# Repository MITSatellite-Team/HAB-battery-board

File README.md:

# HAB-battery-board

Battery board for the MIT Satellite team. Takes in a 2S LiPo and outputs 3.3V + BAT after protecting from overvoltage and undervoltage.

> Made by Nathan Alspaugh
(ndal@mit.edu)

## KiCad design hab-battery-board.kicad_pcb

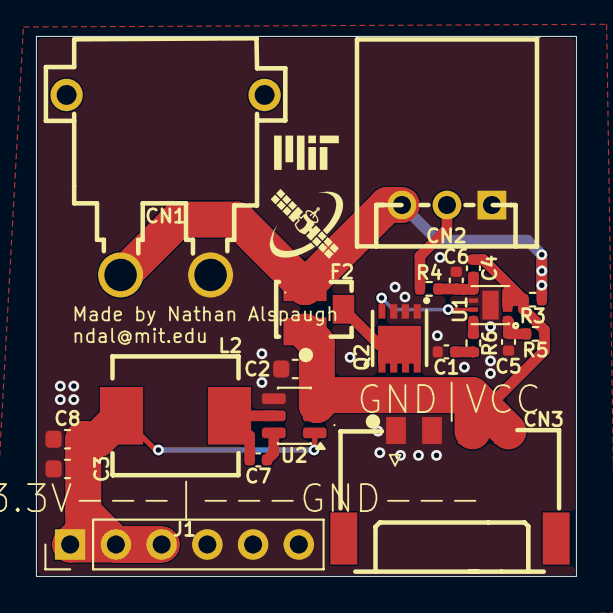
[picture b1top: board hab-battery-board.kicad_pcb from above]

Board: 2 copper layers, 30.0 x 30.0 mm, 21 parts (0 on the bottom side), 13 nets.

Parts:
C1: 470nF; C_0402_1005Metric
C2: 10uF; C_0603_1608Metric
C3, C8: 22uF; C_0603_1608Metric
C4, C5, C6, C7: 100nF; C_0402_1005Metric
CN1: XT30PW-M; CONN-TH_XT30PW-M
CN2: S3B-XH-A; CONN-TH_S3B-XH-A-LF-SN
CN3: 2053380004; CONN-SMD_3P_2053380004
F2: WSFB1514; FUSE-SMD_L4.0-W3.0_SFJ-1412
J1: Conn_01x06_Pin; PinHeader_1x06_P2.54mm_Vertical
L2: FXL0630-4R7-M; IND-SMD_L7.0-W6.6
Q2: AON7506; DFN-8_L3.0-W3.0-P0.65-BL
R3, R4: 1K; R_0402_1005Metric
R5: 100R; R_0402_1005Metric
R6: 5R; R_0402_1005Metric
U1: BQ296227DSGR; WSON-8_L2.0-W2.0-P0.50-TL-EP
U2: AP63203WU; TSOT-23-6

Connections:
+3.3V: C3.1, C8.1, J1.1, J1.2, J1.3, L2.2, U2.1 (FB)
/BAT+: CN1.2 (+), CN2.3, F2.2, R3.1
/BAT_MID: CN2.2, R4.1
GND: C1.2, C2.2, C3.2, C5.2, C6.1, C8.2, CN1.1 (-), CN2.1, CN3.1, CN3.2, J1.4, J1.5, J1.6, Q2.1 (S), Q2.2 (S), Q2.3 (S), U1.6 (VSS), U1.9 (EP), U2.4 (GND)
unnamed: C1.1, R6.2
unnamed: F2.3, Q2.5 (D), Q2.6 (D), Q2.7 (D), Q2.8 (D), Q2.9 (D)
unnamed: Q2.4 (G), U1.7 (OUT)
unnamed: R6.1, U1.8 (REG)
unnamed: C4.1, C6.2, R4.2, U1.5 (V1)
unnamed: C5.1, R5.2, U1.1 (VDD)
unnamed: C7.2, U2.6 (BST)
unnamed: C7.1, L2.1, U2.5 (SW)
VCC: C2.1, C4.2, CN3.3, CN3.4, F2.1, R3.2, R5.1, U1.2 (V4), U1.3 (V3), U1.4 (V2), U2.2 (EN), U2.3 (IN)

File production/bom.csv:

Designator,Footprint,Quantity,Value,LCSC Part #
C1,0402,1,470nF,
C2,0603,1,10uF,
"C3, C8",0603,2,22uF,
"C4, C5, C6, C7",0402,4,100nF,
CN1,CONN-TH_XT30PW-M,1,XT30PW-M,C431092
CN2,CONN-TH_S3B-XH-A-LF-SN,1,S3B-XH-A,C157928
CN3,CONN-SMD_3P_2053380004,1,2053380004,C916325
F2,FUSE-SMD_L4.0-W3.0_SFJ-1412,1,WSFB1514,C42463217
J1,PinHeader_1x06_P2.54mm_Vertical,1,Conn_01x06_Pin,
L2,IND-SMD_L7.0-W6.6,1,FXL0630-4R7-M,C167220
Q2,DFN-8_L3.0-W3.0-P0.65-BL,1,AON7506,C485678
"R3, R4",0402,2,1K,
R5,0402,1,100R,
R6,0402,1,5R,
U1,WSON-8_L2.0-W2.0-P0.50-TL-EP,1,BQ296227DSGR,C3681617
U2,TSOT-23-6,1,AP63203WU,
